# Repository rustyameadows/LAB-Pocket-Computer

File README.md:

# LAB Pocket Computer

[Rev 3A audio revision and volume build budget](hardware/rev-3a/LAB-Pocket-R3A-handoff-r1.md) includes the routed stereo audio update, factory exports and 500- and 1,000-device cost comparisons.

[Rev 3 manufacturing handoff and build costs](hardware/rev-3/LAB-Pocket-R3-manufacturing-handoff-r2.md) covers the corrected switch BOM, factory sourcing holds, prototype budget, KiCad project and upload files.

[Rev 2 bonded-core design](hardware/rev-2/README.md) includes the narrower PCB, matched top-entry card slots, centered camera, exposed Jauch pack and an actual-size review drawing.

A pocket-sized creative computer for making, playing and living with tiny programs.

LAB combines the tactile character of a Pocket Operator, the playful immediacy of a Game Boy, the programmability of a calculator and the openness of a microcontroller development board. It is a platform for small games, visual and musical instruments, personal utilities, experiments and ambient desk displays.

Make an app on your computer, with or without a coding agent. Preview it in a virtual LAB, install it on the physical device, then play with it or leave it on your desk doing something delightful.

## Bare-board Rev A

The [first hardware revision](hardware/rev-a/README.md) includes an editable KiCad project, a full-size fit drawing, a Blender assembly, three renders and the component datasheet archive. Its 82 × 146 mm PCB has fourteen exposed touch pads, sixteen switches and clear outside corners. [Front render](hardware/rev-a/renders/front.png) · [Schematic PDF](hardware/rev-a/review/LAB-Pocket-schematics.pdf)

## Initial hardware direction

- ESP32-S3 host as the original baseline; ESP32-P4 with a separate wireless processor (e.g. ESP32-C6) is the leading camera-capable host candidate.
- Independently programmable RP2350B user processor with its own memory and flash.
- Approximately 2.73-inch square 320 × 320 color IPS display.
- Sixteen tactile buttons with app-specific mappings.
- Proposed dual capacitive touch rails, seven segments on each side of the display (14 independent touch zones).
- Factory-installed, service-replaceable internal microSD (32 GB working target) plus a separate externally accessible microSD expansion/import slot; dedicated firmware flash remains separate.
- Rear-facing programmable color camera: Seeed IMX219 (8 MP MIPI CSI-2) is the lead candidate, with ST VD66GY global shutter (1.5 MP) as a specialized alternative.
- Twelve individually addressable rear-facing RGB LEDs and raised feet for an ambient pool of light.
- USB-C rechargeable power: a thin, service-replaceable ~5,000 mAh flat LiPo is the lead concept; two 21700 Li-ion cells are an alternative form factor with roughly twice the energy and a possible integrated desk stand.
- Four sensitive digital MEMS microphones with independent channels; two ultra-thin stereo speakers (four-speaker alternative) and a required 3.5 mm CTIA TRRS headset jack with stereo output and mono microphone input.
- Bosch BMI270 six-axis IMU and rear-facing Vishay VEML3328 colorscope with white illumination; optional separate ambient light sensor and expansion.
- Raw PCB and enclosed editions.

The host manages the device and its peripherals. The user processor is a playground that developers can program through an SDK, native code or replacement firmware. Independent recovery is a key design goal.

## Documentation

| Document | Purpose |
| --- | --- |
| [Product brief](docs/product-brief.md) | Vision, use cases, product principles and scope |
| [Hardware architecture](docs/hardware-architecture.md) | Dual processors, peripherals, communications, power and recovery |
| [Preliminary BOM](docs/bom.md) | Candidate components, rough unit costs and sourcing assumptions |
| [Developer ecosystem](docs/developer-ecosystem.md) | SDK, virtual device, native development and agent integrations |
| [Starter applications](docs/starter-apps.md) | Candidate built-in apps and what they teach |
| [Prototype roadmap](docs/prototype-roadmap.md) | Learning sequence, benchmarks and decision gates |
| [Industrial design references](docs/design-references.md) | Original notebook sketch and generated open-board concept |

## Project status

Concept and feasibility stage. The current hardware configuration is a working hypothesis, not a finalized design. The original preliminary cost model was $46.40 for a raw-board device at 1,000 units, including assembly, display and battery. The dual-card storage, touch rails, rear camera, revised battery/power system, revised audio and possible host/wireless changes are not yet fully priced; see the updated BOM. These are not supplier quotations.

First milestone: connect development boards, a representative display, buttons and RGB LEDs. Demonstrate a color instrument, responsive 2D graphics, interprocessor communication and recovery from crashed user firmware. Measure performance and power before committing to custom PCBA.

The Rev A schematics and layout are at design-review stage. Production firmware, full routing, supplier qualification and bench validation remain open. Licensing is undecided.

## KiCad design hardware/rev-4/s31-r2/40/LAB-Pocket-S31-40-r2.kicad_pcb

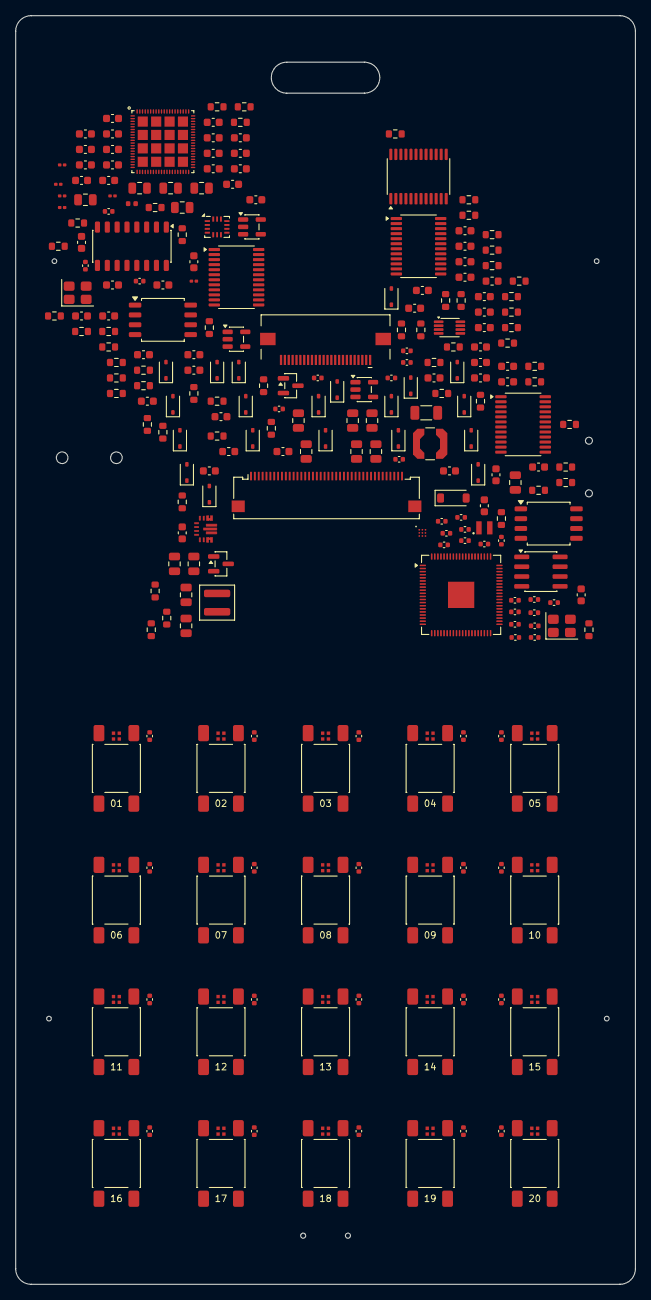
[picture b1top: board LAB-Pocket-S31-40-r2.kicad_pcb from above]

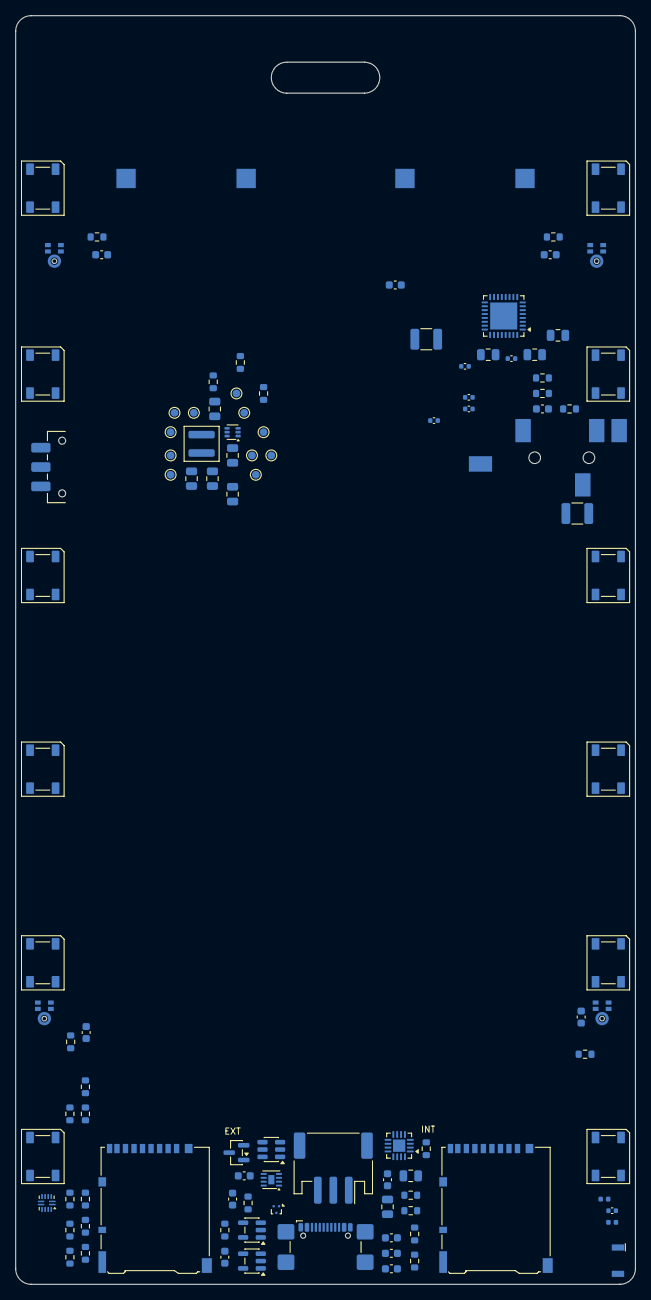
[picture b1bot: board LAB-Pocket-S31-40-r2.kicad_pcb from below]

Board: 8 copper layers, 80.0 x 163.8 mm, 372 parts (106 on the bottom side), 264 nets, no tracks yet.

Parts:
ANT401: 2450AT18A0100001E; Johanson-2450AT18A0100001E
C1, C5, C6, C7, C8, C9, C10, C11, C14, C17, C41, C42, C43, C46, C47, C401, C402, C403, C404, C410, C412, C413, C415, C417, C418, C421, C425, C502, C503, C505, C507, C508, C509, C510, C511, C516, C517: 100n; C_0603_1608Metric
C13: 470n; C_0603_1608Metric
C18, C44, C45, C145, C156, C157, C158, C406, C408, C411, C414, C416, C420, C424, C501, C504: 1u; C_0603_1608Metric
C19, C20, C146, C154, C155: 4.7u; C_0805_2012Metric
C21, C22, C23, C24, C25, C26, C27, C28, C29, C30, C31, C32, C33, C34, C35, C36, C37, C38, C39, C40, C111, C114, C115, C116, C117, C118, C119, C120, C121, C122, C123, C124, C125, C126, C127, C149, C150, C151, C152, C153, C159, C160, C161: 100n; C_0402_1005Metric
C48, C49, C50, C51, C52, C53, C54, C55, C56, C57, C58, C59, C60, C61, C62, C63, C162, C163, C164, C409, C419: 10u; C_0805_2012Metric
C108, C109, C110, C506, C512, C513, C514, C515: 4.7u; C_0402_1005Metric
C112, C113, C422, C423: 15p; C_0603_1608Metric
C147, C148: 100u; C_1210_3225Metric
C405, C407: 10n; C_0603_1608Metric
C426, C427: 1.5p; C_0201_0603Metric
C428: 1p; C_0402_1005Metric
C601, C602, C606: 1 uF / 25 V; C_0603_1608Metric
C603: 2.2 uF / 50 V; C_1206_3216Metric
C604: 330 nF / 16 V; C_0603_1608Metric
C605: 100 nF / 50 V; C_0603_1608Metric
D1, D2, D3, D4, D5, D6, D7, D8, D9, D10, D11, D12, D13, D14, D15, D16, D18, D19, D20, D21: BAS316; D_SOD-323
D22: TPD2EUSB30DRTR; Texas_DRT-3
D601: MBR0540 / Schottky; D_SOD-123
FB501, FB502: 120R at 100 MHz; L_0603_1608Metric
J1: USB4110-GF-A; USB4110-v5
J3: DM3AT • INT; microSD_HC_Hirose_DM3AT-SF-PEJM5
J4: DM3AT • EXT; microSD_HC_Hirose_DM3AT-SF-PEJM5
J5: SJ-43515TS-SMT; SJ-43515TS
J6: JST PH • keyed harness; JST_PH_S3B-PH-SM4-TB_1x03-1MP_P2.00mm_Horizontal
J501: Seeed 114993115 AF flex; JUSHUO_AFC01-S24FCC-00
J601: XF2M-4015-1A / RGB FPC; Omron_XF2M-4015-1A_1x40-1MP_P0.5mm_Horizontal
L1: 1.5uH; L_Coilcraft_XAL4020-XXX
L2: 1.0uH; L_Coilcraft_XAL4020-XXX
L4: 3.3uH; Abracon-AOTA-B201610-R3
L401: 2n / 35mOhm; L_0402_1005Metric
L402: 24n; L_0201_0603Metric
L403: 2.7n; L_0201_0603Metric
L404: 2.7n; L_0402_1005Metric
L405: 3.9n; L_0402_1005Metric
L406: DNP / RF tune; L_0201_0603Metric
L601: 4.7 uH; L_Coilcraft_LPS4018
LED1, LED2, LED3, LED4, LED5, LED6, LED7, LED8, LED9, LED10, LED11, LED12: WS2812B-V6
LED13, LED14, LED15, LED16, LED17, LED18, LED19, LED20, LED21, LED22, LED23, LED24, LED25, LED26, LED27, LED28, LED29, LED30, LED31, LED32: SK6805-EC10-000; SK6805-EC10-v5
LS1, LS2: PUI 8R / 1 W; PUI-AS01808AO-spring-v7
MK1, MK2, MK3, MK4: IM70D122V01; IM70D122
Q1: 2N7002-7-F; SOT-23
Q501: 2N7002; SOT-23
R1, R2, R3, R4, R22, R23, R24, R29, R35, R37, R38, R39, R62, R71, R401, R402, R403, R404, R406, R501, R502, R505, R507, R510, R603, R604: 10k; R_0603_1608Metric
R6, R7, R8, R9, R10, R11, R12, R13, R25, R34, R69: 47k; R_0603_1608Metric
R14, R15, R16, R17, R20: 100R; R_0603_1608Metric
R18, R19, R45, R503, R504, R506: 4.7k; R_0603_1608Metric
R26, R63: 1k; R_0603_1608Metric
R27: 1.5k; R_0603_1608Metric
R30, R33, R44, R47, R72, R73: 100k; R_0603_1608Metric
R31, R70: 1M; R_0603_1608Metric
R32: 169k; R_0603_1608Metric
R36: 68k; R_0603_1608Metric
R40, R41: 1.8M; R_0603_1608Metric
R42: 10.2k; R_0603_1608Metric
R43: 30.9k; R_0603_1608Metric
R46: 732k; R_0603_1608Metric
R61, R605: 33R; R_0603_1608Metric
R68, R74: 2.2k; R_0603_1608Metric
R405: 499; R_0603_1608Metric
R410, R411, R412, R413, R414, R415: 0; R_0603_1608Metric
R416: 0 / RF tune; R_0201_0603Metric
R508, R509: 22R; R_0603_1608Metric
R601: 63.4k; R_0603_1608Metric
R602: 10R; R_0603_1608Metric
SW1, SW2, SW3, SW4, SW5, SW6, SW7, SW8, SW9, SW10, SW11, SW12, SW13, SW14, SW15, SW16, SW17, SW18, SW19, SW20: TL3301; TL3301-key-v5
SW21: System power; SW_SPDT_CK_JS102011SAQN
TP1: RP_SWCLK; TestPoint_Pad_D1.0mm
TP2: RP_SWDIO; TestPoint_Pad_D1.0mm
TP3: RP_RUN_N; TestPoint_Pad_D1.0mm
TP4, TP405: GND; TestPoint_Pad_D1.0mm
TP5, TP406: 3V3; TestPoint_Pad_D1.0mm
TP401: HOST_BOOT_N; TestPoint_Pad_D1.0mm
TP402: HOST_EN; TestPoint_Pad_D1.0mm
TP403: HOST_TX; TestPoint_Pad_D1.0mm
TP404: HOST_RX; TestPoint_Pad_D1.0mm
U1: ESP32-S31NRV16; S31-QFN80
U2: RP2350B; QFN-80-1EP_10x10mm_P0.4mm_EP3.4x3.4mm
U4, U401: PCA9555PWR; TSSOP-24_4.4x7.8mm_P0.65mm
U6: BMI270; Bosch_LGA-14_3x2.5mm_P0.5mm
U8: SN74AHCT1G125DBVR; SOT-23-5
U9, U10: W25Q128JVSIQ; SOIC-8_5.3x5.3mm_P1.27mm
U11: BQ24074RGTR; VQFN-16-1EP_3x3mm_P0.5mm_EP1.6x1.6mm
U12: TPS3700DDCR; TSOT-23-6
U13: MAX17048G+T10; TDFN-8-1EP_2x2mm_P0.5mm_EP0.8x1.2mm
U14: TUSB320LAIRWBR; Texas_X2QFN-12_1.6x1.6mm_P0.4mm
U15: SN74LVC1G04DBVR; SOT-23-5
U16: TLV75533PDBVR; SOT-23-5
U17: TPS3839G33DBZR; SOT-23
U18: TPS63070RNMR; TPS63070-RNM-R3
U19: TPS61023DRLR; SOT-563
U22: APS6404L-3SQR-SN; SOIC-8_3.9x4.9mm_P1.27mm
U31: NAU88C22YG; VQFN-32-1EP_5x5mm_P0.5mm_EP3.5x3.5mm
U32: PAM8406DR; PAM8406-SO16-DS43342
U501: TLV75518PDBVR; SOT-23-5
U502: TLV75728PDBVR; SOT-23-5
U503, U504: SN74AXC8T245PWR; TSSOP-24_4.4x7.8mm_P0.65mm
U505: TCA9406DCUR; VSSOP-8_2.3x2mm_P0.5mm
U601: TPS61163A / dual WLED; TI_YFF0009_TPS61163A
Y1: 40MHz, CL 10pF; Crystal_SMD_3225-4Pin_3.2x2.5mm
Y2: ABM8-272-T3; Crystal_SMD_3225-4Pin_3.2x2.5mm

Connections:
3V3: C1.1, C5.1, C6.1, C7.1, C8.1, C9.1, C10.1, C11.1, C13.1, C17.1, C51.1, C52.1, C53.1, C54.1, C55.1, C56.1, C57.1, C58.1, C108.1, C111.1, C114.1, C115.1, C116.1, C117.1, C118.1, C119.1, C120.1, C121.1, C122.1, C123.1, C124.1, C149.1, C150.1, C151.1, C152.1, C153.1, C154.1, C155.1, C159.1, C160.1, C161.1, C162.1, C163.1, C164.1, C401.1, C402.1, C403.1, C404.1, C405.1, C406.1, C407.1, C408.1, C409.1, C411.1, C412.1, C419.1, C425.1, C508.1, C510.1, C512.1, C514.1, C517.1, C605.1, C606.1, J3.4 (VDD), J4.4 (VDD), J601.5 (VCI), L401.1, MK1.1 (VDD), MK2.1 (VDD), MK2.4 (LR), MK3.1 (VDD), MK4.1 (VDD), MK4.4 (LR), R1.1, R2.1, R3.1, R4.1, R6.1, R7.1, R8.1, R9.1, R10.1, R11.1, R12.1, R13.1, R18.1, R19.1, R22.1, R23.1, R29.1, R37.1, R38.1, R39.1, R43.1, R61.1, R62.1, R70.1, R401.1, R402.1, R403.1, R406.1, R505.2, R507.2, R604.1, TP5.1 (1_1), TP406.1 (PAD_1), U1.11 (VDDPST_1), U1.43 (VCCA/VDDPST_2), U1.54 (VDDPST_3), U1.64 (VDDPST_4), U1.77 (VDDA1), U1.80 (VDDA2), U2.5 (IOVDD), U2.15 (IOVDD), U2.24 (IOVDD), U2.29 (IOVDD), U2.41 (IOVDD), U2.50 (IOVDD), U2.59 (ADC_AVDD), U2.60 (IOVDD), U2.64 (VREG_VIN), U2.68 (USB_OTP_VDD), U2.69 (QSPI_IOVDD), U2.76 (IOVDD), U4.24 (VDD), U6.5 (VDDIO), U6.8 (VDD), U6.12 (CSB), U10.8 (VCC), U18.7 (VOUT), U18.8 (VOUT), U22.8 (VCC), U31.13 (VDDC), U31.14 (VDDB), U31.26 (VDDSPK), U31.31 (VDDA), U32.4 (PVDDL), U32.5 (MUTE_N), U32.6 (VDD), U32.9 (MODE), U32.13 (PVDDR), U401.21 (A0), U401.24 (VCC), U501.1 (IN), U502.1 (IN), U503.1 (VCCA), U504.1 (VCCA), U504.2 (DIR1), U504.11 (DIR2), U505.7 (VCCB)
AMP_AC_L: C156.2, R72.1
AMP_AC_R: C157.2, R73.1
AMP_ENABLE: R74.1, U31.15 (CSB_GPIO1), U32.12 (SHDN_N)
AMP_IN_L: R72.2, U32.7 (INL)
AMP_IN_R: R73.2, U32.10 (INR)
AMP_VREF: C158.1, U32.8 (VREF)
BL_PWM: U1.55 (GPIO42), U601.B1 (PWM)
BMI_ADDR: R71.1, U6.1 (SDO)
BUS_CLK: J3.5 (CLK), J4.5 (CLK), U1.32 (GPIO24/SDIO_CLK), U2.18 (GPIO18)
BUS_MISO: J3.7 (DAT0), J4.7 (DAT0), U1.29 (GPIO22/SDIO_D2), U2.19 (GPIO19)
BUS_MOSI: J3.3 (CMD), J4.3 (CMD), U1.31 (GPIO23/SDIO_D3), U2.16 (GPIO16)
CAM_1V8: C503.1, C509.1, C511.1, C513.1, C516.1, J501.14 (F11_DOVDD), R502.2, U501.5 (OUT), U503.23 (VCCB_1), U503.24 (VCCB_2), U504.23 (VCCB_1), U504.24 (VCCB_2), U505.3 (VCCA), U505.6 (OE)
CAM_2V8: C515.1, FB501.1, FB502.1, U502.5 (OUT)
CAM_AF_2V8: C506.1, C507.1, FB502.2, J501.1 (F24_AFVDD)
CAM_ANALOG_ENABLE: Q501.1 (G), R504.1, U401.10 (P06), U502.3 (EN)
CAM_AVDD_2V8: C504.1, C505.1, FB501.2, J501.21 (F04_AVDD)
CAM_BUS_OE_N: Q501.3 (D), R507.1, U503.22 (OE_N), U504.22 (OE_N)
CAM_D0: U1.59 (GPIO46), U503.3 (A1)
CAM_D0_1V8: J501.6 (F19_Y2), U503.21 (B1)
CAM_D1: U1.60 (GPIO47), U503.4 (A2)
CAM_D1_1V8: J501.4 (F21_Y3), U503.20 (B2)
CAM_D2: U1.61 (GPIO48), U503.5 (A3)
CAM_D2_1V8: J501.3 (F22_Y4), U503.19 (B3)
CAM_D3: U1.62 (GPIO49), U503.6 (A4)
CAM_D3_1V8: J501.5 (F20_Y5), U503.18 (B4)
CAM_D4: U1.65 (GPIO50), U503.7 (A5)
CAM_D4_1V8: J501.7 (F18_Y6), U503.17 (B5)
CAM_D5: U1.66 (GPIO51), U503.8 (A6)
CAM_D5_1V8: J501.9 (F16_Y7), U503.16 (B6)
CAM_D6: U1.67 (GPIO52), U503.9 (A7)
CAM_D6_1V8: J501.11 (F14_Y8), U503.15 (B7)
CAM_D7: U1.68 (GPIO53), U503.10 (A8)
CAM_D7_1V8: J501.13 (F12_Y9), U503.14 (B8)
CAM_DVDD_INT: C501.1, C502.1, J501.15 (F10_DVDD_INT)
CAM_ENABLE: R503.1, U4.18 (IO1_5), U501.3 (EN)
CAM_HREF: U1.72 (GPIO57/MTMS), U504.8 (A6)
CAM_HREF_1V8: J501.16 (F09_HREF), U504.16 (B6)
CAM_PCLK: R509.2, U1.69 (GPIO54/MTDO)
CAM_PCLK_1V8: J501.8 (F17_PCLK), U504.17 (B5)
CAM_PCLK_DRV: R509.1, U504.7 (A5)
CAM_PWDN: R505.1, U401.9 (P05), U504.4 (A2)
CAM_PWDN_1V8: J501.17 (F08_PWDN), R502.1, U504.20 (B2)
CAM_RESET_N: R506.1, U401.8 (P04), U504.5 (A3)
CAM_RESET_N_1V8: J501.19 (F06_RESETB), R501.1, U504.19 (B3)
CAM_SCL_1V8: J501.20 (F05_SCL), U505.5 (SCL_A)
CAM_SDA_1V8: J501.22 (F03_SDA), U505.4 (SDA_A)
CAM_VSYNC: U1.71 (GPIO56/MTDI), U504.9 (A7)
CAM_VSYNC_1V8: J501.18 (F07_VSYNC), U504.15 (B7)
CAM_XCLK: R510.1, U1.70 (GPIO55/MTCK), U504.3 (A1)
CAM_XCLK_1V8: J501.12 (F13_MCLK), R508.2
CAM_XCLK_DRV_1V8: R508.1, U504.21 (B1)
CC1: J1.A5 (CC1), U14.1 (CC1)
CC2: J1.B5 (CC2), U14.2 (CC2)
CC_3V3: C43.1, C44.1, C46.1, R24.1, U14.12 (VDD), U15.5 (VCC), U16.5 (OUT)
CC_HIGH_N: R24.2, U14.7 (OUT1), U15.2 (A)
CC_VBUS_DET: R40.2, R41.2, U14.4 (VBUS_DET)
CHARGE_TIMER: R36.1, U11.14 (TMR)
CHARGING_N: R39.2, U4.9 (IO0_5), U11.9 (~CHG)
CHG_CE_N: Q1.3 (D), R35.2, U11.4 (~CE)
CHG_ISET: R26.1, U11.16 (ISET)
CODEC_VMID: C146.1, U31.27 (VREF)
COLD_SENSE: R32.2, R33.1, U12.4 (INB-)
FUEL_ALERT_N: R37.2, U4.11 (IO0_7), U13.5 (ALRT)
GND: C1.2, C5.2, C6.2, C7.2, C8.2, C9.2, C10.2, C11.2, C13.2, C14.2, C17.2, C18.2, C19.2, C20.2, C21.2, C22.2, C23.2, C24.2, C25.2, C26.2, C27.2, C28.2, C29.2, C30.2, C31.2, C32.2, C33.2, C34.2, C35.2, C36.2, C37.2, C38.2, C39.2, C40.2, C41.2, C42.2, C43.2, C44.2, C45.2, C46.2, C47.2, C48.2, C49.2, C50.2, C51.2, C52.2, C53.2, C54.2, C55.2, C56.2, C57.2, C58.2, C59.2, C60.2, C61.2, C62.2, C63.2, C108.2, C109.2, C110.2, C111.2, C112.2, C113.2, C114.2, C115.2, C116.2, C117.2, C118.2, C119.2, C120.2, C121.2, C122.2, C123.2, C124.2, C125.2, C126.2, C127.2, C146.2, C149.2, C150.2, C151.2, C152.2, C153.2, C154.2, C155.2, C158.2, C159.2, C160.2, C161.2, C162.2, C163.2, C164.2, C401.2, C402.2, C403.2, C404.2, C405.2, C406.2, C407.2, C408.2, C409.2, C410.2, C411.2, C412.2, C413.2, C414.2, C415.2, C416.2, C417.2, C418.2, C419.2, C420.2, C421.2, C422.2, C423.2, C424.2, C425.2, C426.2, C427.2, C501.2, C502.2, C503.2, C504.2, C505.2, C506.2, C507.2, C508.2, C509.2, C510.2, C511.2, C512.2, C513.2, C514.2, C515.2, C516.2, C517.2, C601.2, C602.2, C603.2, C604.2, C605.2, C606.2, D22.3 (GND), J1.A1 (GND), J1.A12 (GND), J1.B1 (GND), J1.B12 (GND), J1.SH (SHIELD), J3.6 (VSS), J3.10 (DET_A), J3.SH (SHIELD), J4.6 (VSS), J4.10 (DET_A), J4.SH (SHIELD), J5.4 (Ring2), J6.1, J501.2 (F23_AF_GND), J501.10 (F15_DGND), J501.23 (F02_AGND), J501.25 (HOLD_L), J501.26 (HOLD_R), J601.4 (GND), J601.16 (B0), J601.28 (R0), J601.34 (GND), J601.40 (GND), L404.2, L406.2, LED1.3 (VSS), LED2.3 (VSS), LED3.3 (VSS), LED4.3 (VSS), LED5.3 (VSS), LED6.3 (VSS), LED7.3 (VSS), LED8.3 (VSS), LED9.3 (VSS), LED10.3 (VSS), LED11.3 (VSS), LED12.3 (VSS), LED13.1 (VSS), LED14.1 (VSS), LED15.1 (VSS), LED16.1 (VSS), LED17.1 (VSS), LED18.1 (VSS), LED19.1 (VSS), LED20.1 (VSS), LED21.1 (VSS), LED22.1 (VSS), LED23.1 (VSS), LED24.1 (VSS), LED25.1 (VSS), LED26.1 (VSS), LED27.1 (VSS), LED28.1 (VSS), LED29.1 (VSS), LED30.1 (VSS), LED31.1 (VSS), LED32.1 (VSS), MK1.4 (LR), MK1.5 (GND), MK2.5 (GND), MK3.4 (LR), MK3.5 (GND), MK4.5 (GND), Q1.2 (S), Q501.2 (S), R25.2, R26.2, R27.2, R31.2, R33.2, R36.2, R42.2, R44.2, R45.2, R47.2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
HEADSET_MIC: C145.1, J5.1 (Sleeve), R68.2
HOST_BOOT_N: R402.2, TP401.1 (PAD_1), U1.76 (GPIO61)
HOST_EN: C424.1, R401.2, TP402.1 (PAD_1), U1.4 (CHIP_PU)
HOST_FLASH_VDD: C420.1, C421.1, R404.1, U1.39 (VDD_SPI), U9.8 (VCC)
HOST_NOR_CLK: R414.2, U9.6 (CLK)
HOST_NOR_CS_N: R404.2, R410.2, U9.1 (CS#)
HOST_NOR_D0: R415.2, U9.5 (DI/IO0)
HOST_NOR_D1: R411.2, U9.2 (DO/IO1)
HOST_NOR_D2: R412.2, U9.3 (WP#/IO2)
HOST_NOR_D3: R413.2, U9.7 (HOLD#/IO3)
HOST_RX: TP404.1 (PAD_1), U1.74 (GPIO59/U0RXD)
HOST_TX: R405.2, TP403.1 (PAD_1)
HOST_XTAL_N: C423.1, U1.78 (XTAL_N), Y1.3 (XTAL)
HOST_XTAL_P: C422.1, L402.2, Y1.1 (XTAL)
HOT_SENSE: R30.2, R31.1, U12.3 (INA+)
HP_L: C147.2, J5.2 (Tip), R69.1
HP_R: C148.2, J5.3 (Ring1)
HP_RAW_L: C147.1, U31.30 (LHP)
HP_RAW_R: C148.1, U31.29 (RHP)
HP_TIP_SWITCH: J5.5 (TipSwitch), R70.2, U31.3 (LLIN_GPIO2)
I2S_ADC: U1.27 (GPIO20/SDIO_D0), U31.9 (ADCOUT)
I2S_BCLK: U1.12 (GPIO6), U31.8 (BCLK)
I2S_DAC: U1.28 (GPIO21/SDIO_D1), U31.10 (DACIN)
I2S_LRCLK: U1.13 (GPIO7), U31.7 (FS)
I2S_MCLK: U1.10 (GPIO5), U31.11 (MCLK)
ILIM_SET: R27.1, U11.12 (ILIM)
IMU_INT: U1.51 (GPIO38), U6.4 (INT1)
KEY_C0: R1.2, SW1.2, SW6.2, SW11.2, SW16.2, U4.13 (IO1_0)
KEY_C1: R2.2, SW2.2, SW7.2, SW12.2, SW17.2, U4.14 (IO1_1)
KEY_C2: R3.2, SW3.2, SW8.2, SW13.2, SW18.2, U4.15 (IO1_2)
KEY_C3: R4.2, SW4.2, SW9.2, SW14.2, SW19.2, U4.16 (IO1_3)
KEY_C4: R29.2, SW5.2, SW10.2, SW15.2, SW20.2, U4.17 (IO1_4)
KEY_R0: D1.1 (K), D2.1 (K), D3.1 (K), D4.1 (K), D5.1 (K), U4.4 (IO0_0)
KEY_R1: D6.1 (K), D7.1 (K), D8.1 (K), D9.1 (K), D10.1 (K), U4.5 (IO0_1)
KEY_R2: D11.1 (K), D12.1 (K), D13.1 (K), D14.1 (K), D15.1 (K), U4.6 (IO0_2)
KEY_R3: D16.1 (K), D18.1 (K), D19.1 (K), D20.1 (K), D21.1 (K), U4.7 (IO0_3)
KEY_RGB_01: LED13.4 (DOUT), LED14.2 (DIN)
KEY_RGB_02: LED14.4 (DOUT), LED15.2 (DIN)
KEY_RGB_03: LED15.4 (DOUT), LED16.2 (DIN)
KEY_RGB_04: LED16.4 (DOUT), LED17.2 (DIN)
KEY_RGB_05: LED17.4 (DOUT), LED18.2 (DIN)
KEY_RGB_06: LED18.4 (DOUT), LED19.2 (DIN)
KEY_RGB_07: LED19.4 (DOUT), LED20.2 (DIN)
KEY_RGB_08: LED20.4 (DOUT), LED21.2 (DIN)
KEY_RGB_09: LED21.4 (DOUT), LED22.2 (DIN)
KEY_RGB_10: LED22.4 (DOUT), LED23.2 (DIN)
KEY_RGB_11: LED23.4 (DOUT), LED24.2 (DIN)
KEY_RGB_12: LED24.4 (DOUT), LED25.2 (DIN)
KEY_RGB_13: LED25.4 (DOUT), LED26.2 (DIN)
KEY_RGB_14: LED26.4 (DOUT), LED27.2 (DIN)
KEY_RGB_15: LED27.4 (DOUT), LED28.2 (DIN)
KEY_RGB_16: LED28.4 (DOUT), LED29.2 (DIN)
KEY_RGB_17: LED29.4 (DOUT), LED30.2 (DIN)
KEY_RGB_18: LED30.4 (DOUT), LED31.2 (DIN)
KEY_RGB_19: LED31.4 (DOUT), LED32.2 (DIN)
KEY_RGB_IN: LED12.2 (DOUT), LED13.2 (DIN)
LCD_B0: J601.17 (B1), U1.14 (GPIO8)
LCD_B1: J601.18 (B2), U1.15 (GPIO9)
LCD_B2: J601.19 (B3), U1.16 (GPIO10)
LCD_B3: J601.20 (B4), U1.17 (GPIO11)
LCD_B4: J601.21 (B5), U1.19 (GPIO12)
LCD_BL_COMP: C604.1, U601.B2 (COMP)
LCD_BL_ISET: R601.1, U601.A1 (ISET)
LCD_BL_SW: D601.2 (A), L601.2, U601.C3 (SW)
LCD_BL_VIN: C602.1, R602.2, U601.C1 (EN), U601.C2 (VIN)
LCD_CS: J601.11 (CS), R604.2, U401.4 (P00)
LCD_DE: J601.13 (DE), U1.56 (GPIO43)
LCD_G0: J601.22 (G0), U1.20 (GPIO13)
LCD_G1: J601.23 (G1), U1.21 (GPIO14)
LCD_G2: J601.24 (G2), U1.22 (GPIO15)
LCD_G3: J601.25 (G3), U1.23 (GPIO16)
LCD_G4: J601.26 (G4), U1.24 (GPIO17)
LCD_G5: J601.27 (G5), U1.25 (GPIO18)
LCD_HSYNC: J601.15 (HSYNC), U1.57 (GPIO44)
LCD_LED_A: C603.1, D601.1 (K), J601.1 (LEDA)
LCD_LED_K1: J601.2 (LEDK1), U601.A3 (IFB1)
LCD_LED_K2: J601.3 (LEDK2), U601.A2 (IFB2)
LCD_PCLK: R605.1, U1.53 (GPIO40)
LCD_PCLK_FPC: J601.12 (PCLK), R605.2
LCD_R0: J601.29 (R1), U1.26 (GPIO19)
LCD_R1: J601.30 (R2), U1.46 (GPIO33)
LCD_R2: J601.31 (R3), U1.47 (GPIO34)
LCD_R3: J601.32 (R4), U1.48 (GPIO35)
LCD_R4: J601.33 (R5), R403.2, U1.49 (GPIO36)
LCD_RESET_N: J601.6 (RESET), R603.1, U401.7 (P03)
LCD_SCK: J601.10 (SCK), U401.5 (P01)
LCD_SDI: J601.9 (SDA), U401.6 (P02)
LCD_VSYNC: J601.14 (VSYNC), U1.58 (GPIO45)
LED_5V_SW: C14.1, C21.1, C22.1, C23.1, C24.1, C25.1, C26.1, C27.1, C28.1, C29.1, C30.1, C31.1, C32.1, C33.1, C34.1, C35.1, C36.1, C37.1, C38.1, C39.1, C40.1, C61.1, C62.1, C63.1, LED1.1 (VDD), LED2.1 (VDD), LED3.1 (VDD), LED4.1 (VDD), LED5.1 (VDD), LED6.1 (VDD), LED7.1 (VDD), LED8.1 (VDD), LED9.1 (VDD), LED10.1 (VDD), LED11.1 (VDD), LED12.1 (VDD), LED13.3 (VDD), LED14.3 (VDD), LED15.3 (VDD), LED16.3 (VDD), LED17.3 (VDD), LED18.3 (VDD), LED19.3 (VDD), LED20.3 (VDD), LED21.3 (VDD), LED22.3 (VDD), LED23.3 (VDD), LED24.3 (VDD), LED25.3 (VDD), LED26.3 (VDD), LED27.3 (VDD), LED28.3 (VDD), LED29.3 (VDD), LED30.3 (VDD), LED31.3 (VDD), LED32.3 (VDD), R46.1, U8.5 (VCC), U19.6 (VOUT)
LED_ENABLE: R45.1, U4.8 (IO0_4), U19.2 (EN)
LINE_L: C156.1, U31.22 (AUXOUT2)
LINE_R: C157.1, U31.21 (AUXOUT1)
MIC_AC: C145.2, U31.1 (LMICP)
MIC_BIAS: R68.1, U31.32 (MICBIAS)
MIC_RAW_1: MK1.3 (DATA), R14.1
MIC_RAW_2: MK2.3 (DATA), R15.1
MIC_RAW_3: MK3.3 (DATA), R16.1
MIC_RAW_4: MK4.3 (DATA), R17.1
unnamed: D1.2 (A), SW1.1
unnamed: D2.2 (A), SW2.1
unnamed: D3.2 (A), SW3.1
unnamed: D4.2 (A), SW4.1
unnamed: D5.2 (A), SW5.1
unnamed: D6.2 (A), SW6.1
unnamed: D7.2 (A), SW7.1
unnamed: D8.2 (A), SW8.1
unnamed: D9.2 (A), SW9.1
unnamed: D10.2 (A), SW10.1
unnamed: D11.2 (A), SW11.1
unnamed: D12.2 (A), SW12.1
unnamed: D13.2 (A), SW13.1
unnamed: D14.2 (A), SW14.1
unnamed: D15.2 (A), SW15.1
unnamed: D16.2 (A), SW16.1
unnamed: D18.2 (A), SW17.1
unnamed: D19.2 (A), SW18.1
unnamed: D20.2 (A), SW19.1
unnamed: D21.2 (A), SW20.1
unnamed: LED1.2 (DOUT), LED2.4 (DIN)
unnamed: LED2.2 (DOUT), LED3.4 (DIN)
unnamed: LED3.2 (DOUT), LED4.4 (DIN)
unnamed: LED5.2 (DOUT), LED6.4 (DIN)
unnamed: LED6.2 (DOUT), LED7.4 (DIN)
unnamed: LED7.2 (DOUT), LED8.4 (DIN)
unnamed: LED9.2 (DOUT), LED10.4 (DIN)
unnamed: LED10.2 (DOUT), LED11.4 (DIN)
unnamed: LED11.2 (DOUT), LED12.4 (DIN)
PACK_POS: C20.1, C42.1, J6.3, U11.2 (BAT), U11.3 (BAT), U13.2 (CELL), U13.3 (VDD)
PACK_TS: J6.2, R30.1, R32.1, U11.1 (TS)
PDM_A: R14.2, R15.2, U1.5 (GPIO0/XTAL32_N)
PDM_B: R16.2, R17.2, U1.6 (GPIO1/XTAL32_P)
PDM_CLK: MK1.2 (CLK), MK2.2 (CLK), MK3.2 (CLK), MK4.2 (CLK), U1.9 (GPIO4)
PIXEL_FB: R46.2, R47.1, U19.1 (FB)
PIXEL_SW: L2.2, U19.5 (SW)
REG_AUX: C47.1, U18.3 (VAUX)
REG_FB: R42.1, R43.2, U18.5 (FB)
REG_L1: L1.1, U18.11 (L1)
REG_L2: L1.2, U18.9 (L2)
RF_ANT_FEED: ANT401.1 (FEED_1), L405.2
RF_FEED_50R: C428.1, L406.1, R416.2
RF_TEE: C428.2, L404.1, L405.1
RGB_DATA_3V3: U1.52 (GPIO39), U8.2 (A)
RGB_DRIVE_5V: R20.1, U8.4 (Y)
RGB_IN: LED1.4 (DIN), R20.2
RGB_LINK_4: LED4.2 (DOUT), LED5.4 (DIN)
RGB_LINK_8: LED8.2 (DOUT), LED9.4 (DIN)
RP_CORE: C109.1, C125.1, C126.1, C127.1, L4.1, U2.10 (DVDD), U2.32 (DVDD), U2.51 (DVDD), U2.65 (VREG_FB)
RP_CS_N: R406.2, U1.33 (GPIO25/SDIO_CMD), U2.17 (GPIO17)
RP_RAM_CS_N: R62.2, U2.77 (GPIO0), U22.1 (CE_N)
RP_REG_AVDD: C110.1, R61.2, U2.61 (VREG_AVDD)
RP_REG_LX: L4.2, U2.63 (VREG_LX)
RP_RUN_N: R22.2, TP3.1 (1_1), U2.35 (RUN), U401.11 (P07)
RP_SWCLK: TP1.1 (1_1), U2.33 (SWCLK)
RP_SWDIO: TP2.1 (1_1), U2.34 (SWDIO)
RP_XIN: C112.1, U2.30 (XIN), Y2.1 (X1)
RP_XOUT: R63.1, U2.31 (XOUT)
RP_XTAL_2: C113.1, R63.2, Y2.3 (X2)
S31_ADC_REF: C418.1, U1.63 (VREF_ADC)
S31_ANT: C426.1, L403.1, U1.1 (ANT)
S31_NOR_CLK: R414.1, U1.41 (SPICLK)
S31_NOR_CS_N: R410.1, U1.36 (SPICS)
S31_NOR_D0: R415.1, U1.42 (SPID)
S31_NOR_D1: R411.1, U1.37 (SPIQ)
S31_NOR_D2: R412.1, U1.38 (SPIWP)
S31_NOR_D3: R413.1, U1.40 (SPIHD)
S31_PSRAM_1V8: C413.1, C414.1, C415.1, C416.1, C417.1, U1.30 (VDD_PSRAM_1P8_1), U1.34 (VDD_PSRAM_1P8_2), U1.35 (VDD_LDO_1P8)
S31_RF_MATCH: C427.1, L403.2, R416.1
S31_RF_VDD: C410.1, L401.2, U1.2 (VDDA3), U1.3 (VDDA4)
S31_UART0_TX: R405.1, U1.73 (GPIO58/U0TXD)
S31_XTAL_P: L402.1, U1.79 (XTAL_P)
SD_EXT_CS_N: J4.2 (DAT3/CD), R11.2, U1.75 (GPIO60)
SD_EXT_DAT1: J4.8 (DAT1), R12.2
SD_EXT_DAT2: J4.1 (DAT2), R10.2
SD_EXT_DET_N: J4.9 (DET_B), R13.2, U401.13 (P10)
SD_INT_CS_N: J3.2 (DAT3/CD), R7.2, U1.50 (GPIO37)
SD_INT_DAT1: J3.8 (DAT1), R8.2
SD_INT_DAT2: J3.1 (DAT2), R6.2
SD_INT_DET_N: J3.9 (DET_B), R9.2, U401.14 (P11)
SPK_L_N: LS1.2 (Minus), U32.3 (OUT_L_N)
SPK_L_P: LS1.1 (Plus), U32.1 (OUT_L_P)
SPK_R_N: LS2.2 (Minus), U32.14 (OUT_R_N)
SPK_R_P: LS2.1 (Plus), U32.16 (OUT_R_P)
SYSTEM_ENABLE: R44.1, SW21.2 (B), U18.14 (EN)
SYS_ABOVE_UVLO: SW21.3 (C), U17.2 (RESET_N)
SYS_SCL: R19.2, U1.8 (GPIO3), U4.22 (SCL), U6.13 (SCx), U13.7 (SCL), U31.16 (SCLK), U401.22 (SCL), U505.8 (SCL_B)
SYS_SDA: R18.2, U1.7 (GPIO2), U4.23 (SDA), U6.14 (SDx), U13.8 (SDA), U31.17 (SDIO), U401.23 (SDA), U505.1 (SDA_B)
TEMP_OK: Q1.1 (G), R34.2, U12.1 (OUTA), U12.6 (OUTB)
USB_D_N: D22.2 (D_N), J1.A7 (D-), J1.B7 (D-), U1.45 (USB_DM)
USB_D_P: D22.1 (D_P), J1.A6 (D+), J1.B6 (D+), U1.44 (USB_DP)
USB_HIGH_CURRENT: R25.1, U11.5 (EN2), U15.4 (Y)
USER_NOR_CLK: U2.71 (QSPI_SCLK), U10.6 (CLK), U22.6 (SCLK)
USER_NOR_CS_N: R23.2, U2.75 (~QSPI_SS), U10.1 (CS_N)
USER_NOR_D0: U2.72 (QSPI_SD0), U10.5 (IO0), U22.5 (SIO0)
USER_NOR_D1: U2.74 (QSPI_SD1), U10.2 (IO1), U22.2 (SIO1)
USER_NOR_D2: U2.73 (QSPI_SD2), U10.3 (IO2), U22.3 (SIO2)
USER_NOR_D3: U2.70 (QSPI_SD3), U10.7 (IO3), U22.7 (SIO3)
VBUS: C18.1, C41.1, C45.1, J1.A4 (VBUS), J1.A9 (VBUS), J1.B4 (VBUS), J1.B9 (VBUS), R34.1, R40.1, R41.1, U11.13 (IN), U12.5 (VDD), U16.1 (IN), U16.3 (EN)
VBUS_OK_N: R38.2, U4.10 (IO0_6), U11.7 (~PGOOD)
VSYS: C19.1, C48.1, C49.1, C50.1, C59.1, C60.1, C601.1, L2.1, L601.1, R35.1, R602.1, U11.10 (OUT), U11.11 (OUT), U17.3 (VDD), U18.12 (VIN), U18.13 (VIN), U19.3 (VIN)

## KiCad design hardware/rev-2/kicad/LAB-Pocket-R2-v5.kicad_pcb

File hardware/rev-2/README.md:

# LAB Pocket Computer · Rev 2

The Rev 2 bare board measures **74 × 146 mm**. The exposed Jauch pack bonds to the rear PCB. The nominal maximum-cycled stack is **14.97 mm** from the front display surface to the back of the pouch. Rev A measured 82 × 146 × 20.55 mm.

[Actual-size US Letter drawing](review/LAB-Pocket-R2-letter-v1-core.pdf) · [Rear render](renders/LAB-Pocket-R2-rear.png) · [Front render](renders/LAB-Pocket-R2-front.png) · [Full Blender assembly](blender/LAB-Pocket-R2.blend) · [Assembled GLB](blender/LAB-Pocket-R2-assembled.glb) · [KiCad project](kicad/LAB-Pocket-R2.kicad_pro) · [Nine schematic sheets](review/LAB-Pocket-R2-schematics.pdf)

## Mechanical layout

- The 59.5 mm pouch width sets the board width. Each side adds a 1.25 mm pouch-to-LED gap, a 5 mm LED body and 1 mm from that body to the PCB edge. The 53.54 mm LCD leaves 1.43 mm between its body and each 7.6 mm touch electrode. Switches retain their 17 × 16 mm pitch. All sixteen have individual references on the drawing.
- Both rear Hirose slots open toward the short top edge. From the rear, external J4 is on the left and internal J3 is on the right. Their origin points are 22 mm to either side of the centerline and 20.2 mm down from the top. Each slot has a clear card approach. J3 includes the seated card.
- The twelve LEDs form two six-pixel columns. LED12 starts at the upper left in rear view. Centers are 3.5 mm from the side edges, at 10.5, 35.5, 60.5, 85.5, 110.5 and 135.5 mm down the board. The top microphones moved below the top LEDs to keep the card approaches clear.
- The rear lens is directly behind the center of the active display at **37.00 mm from either side and 37.06 mm from the top**. This leaves 1.69 mm from the nominal camera carrier to the pouch. The headset jack moved to the lower side and the speakers moved down 3 mm for clearance.
- The guard, four feet, tabs, studs and guard mounting holes have been removed. The pouch is the outermost surface on the back.

## Pack and bond

The 4,800 mAh LP735977JH has a 59.5 × 78.5 mm maximum footprint. Jauch specifies 7.3 mm at delivery and 7.9 mm after cycling. The model uses the cycled envelope and includes a folded laminate rim, a shallow protection-board end, two separate wire exits, and label artwork taken from the manufacturer's drawing. The short-end details are visual approximations. Each modeled lead is 70 mm from its pad to its J6 terminal. The service loops and termination are proposed integration geometry. The supplier part comes with wire leads. [Jauch source drawing, p. 1](datasheets/LP735977JH.pdf)

Two candidate 20 × 55 mm strips of 3M 9495LE bond the pack to the rear solder mask. The installed tape thickness is 0.17 mm. The dimensional stack is 6.90 mm from the back of the PCB to the front display, plus 0.17 mm of bondline and 7.90 mm of pouch. The pack area excludes rear components and the matrix vias are tented on the pack side. [3M technical data](datasheets/3M-9495LE.pdf)

Confirm wrapper-to-adhesive compatibility with the pack supplier and validate retention, swelling clearance, insulation and wire dressing on a physical sample. The exposed pouch and its protection circuitry remain accessible to contact. Pocket carry, drops and abrasion require mechanical validation.

## Review status

KiCad and Blender checks confirm the dimensions above. PCB DRC reports **zero courtyard overlaps, keepout violations, shorts or schematic-parity mismatches**. Electrical completion is open. There are 388 unrouted connections and 108 inherited DRC violations, comprising 104 ESP32-P4 pad-clearance violations and four USB-C pad-to-hole clearance violations. ERC reports 143 errors and 18 warnings. Camera electrical integration, power, clocking, radio and high-speed routing require further work. Charging remains inhibited in the study schematic.

Run the board checker with the system Python containing KiCad 10's pcbnew module. The Blender checker reads the evaluated assembly at frame 1. The assembled GLB uses metres, while the Blender scene and drawing use millimetres. The second GLB contains the KiCad board export alone.

```sh
/usr/bin/python3 check-fit-R2.py
blender -b blender/LAB-Pocket-R2.blend --python-exit-code 1 -P check-scene-R2.py
```

[Rev 2 BOM](parts.csv) · [Index and SHA-256 digests for all 32 supplier documents](datasheets/index.csv)

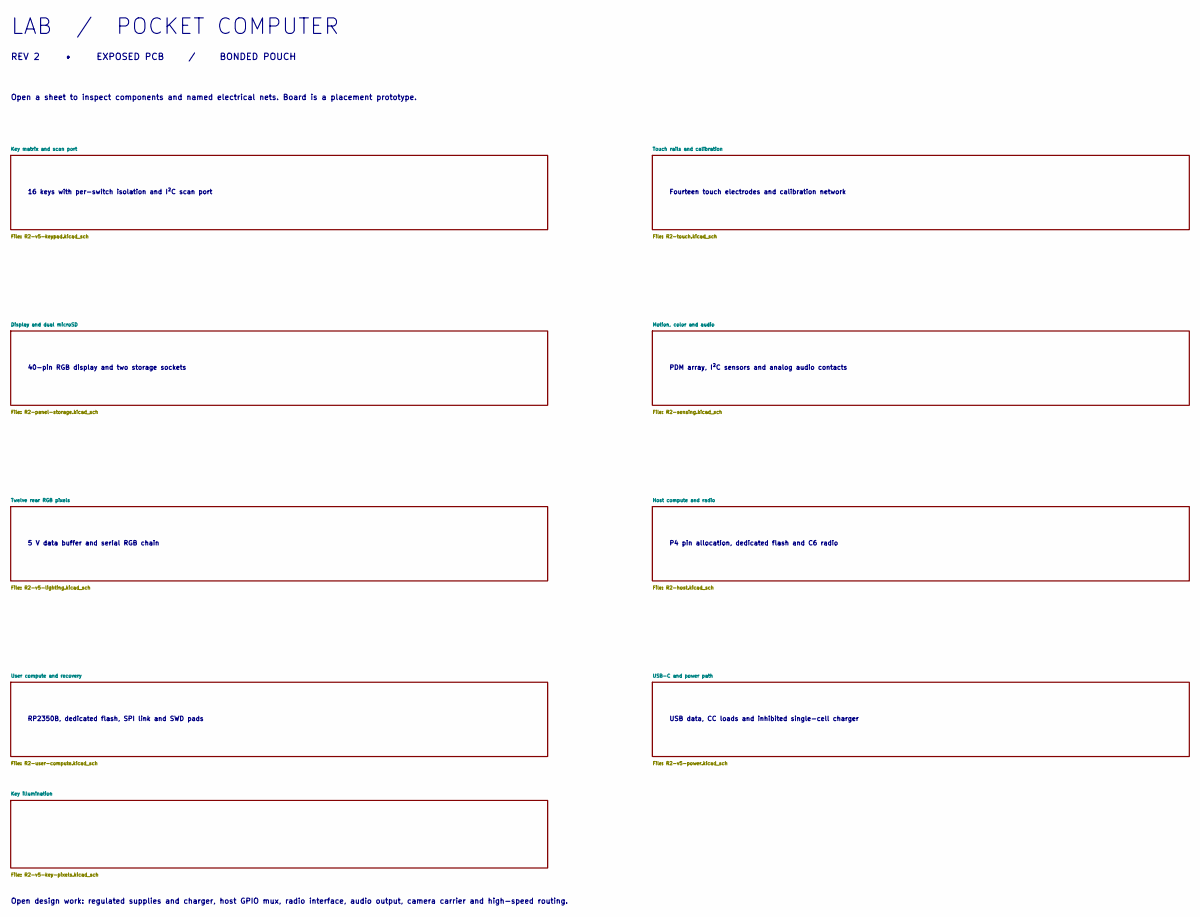
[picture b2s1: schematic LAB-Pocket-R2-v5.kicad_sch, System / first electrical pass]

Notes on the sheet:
LAB / POCKET COMPUTER
REV 2 • EXPOSED PCB / BONDED POUCH
Open a sheet to inspect components and named electrical nets. Board is a placement prototype.
16 keys with per-switch isolation and I²C scan port
Fourteen touch electrodes and calibration network
40-pin RGB display and two storage sockets
PDM array, I²C sensors and analog audio contacts
5 V data buffer and serial RGB chain
P4 pin allocation, dedicated flash and C6 radio
RP2350B, dedicated flash, SPI link and SWD pads
USB data, CC loads and inhibited single-cell charger
Open design work: regulated supplies and charger, host GPIO mux, radio interface, audio output, camera carrier and high-speed routing.

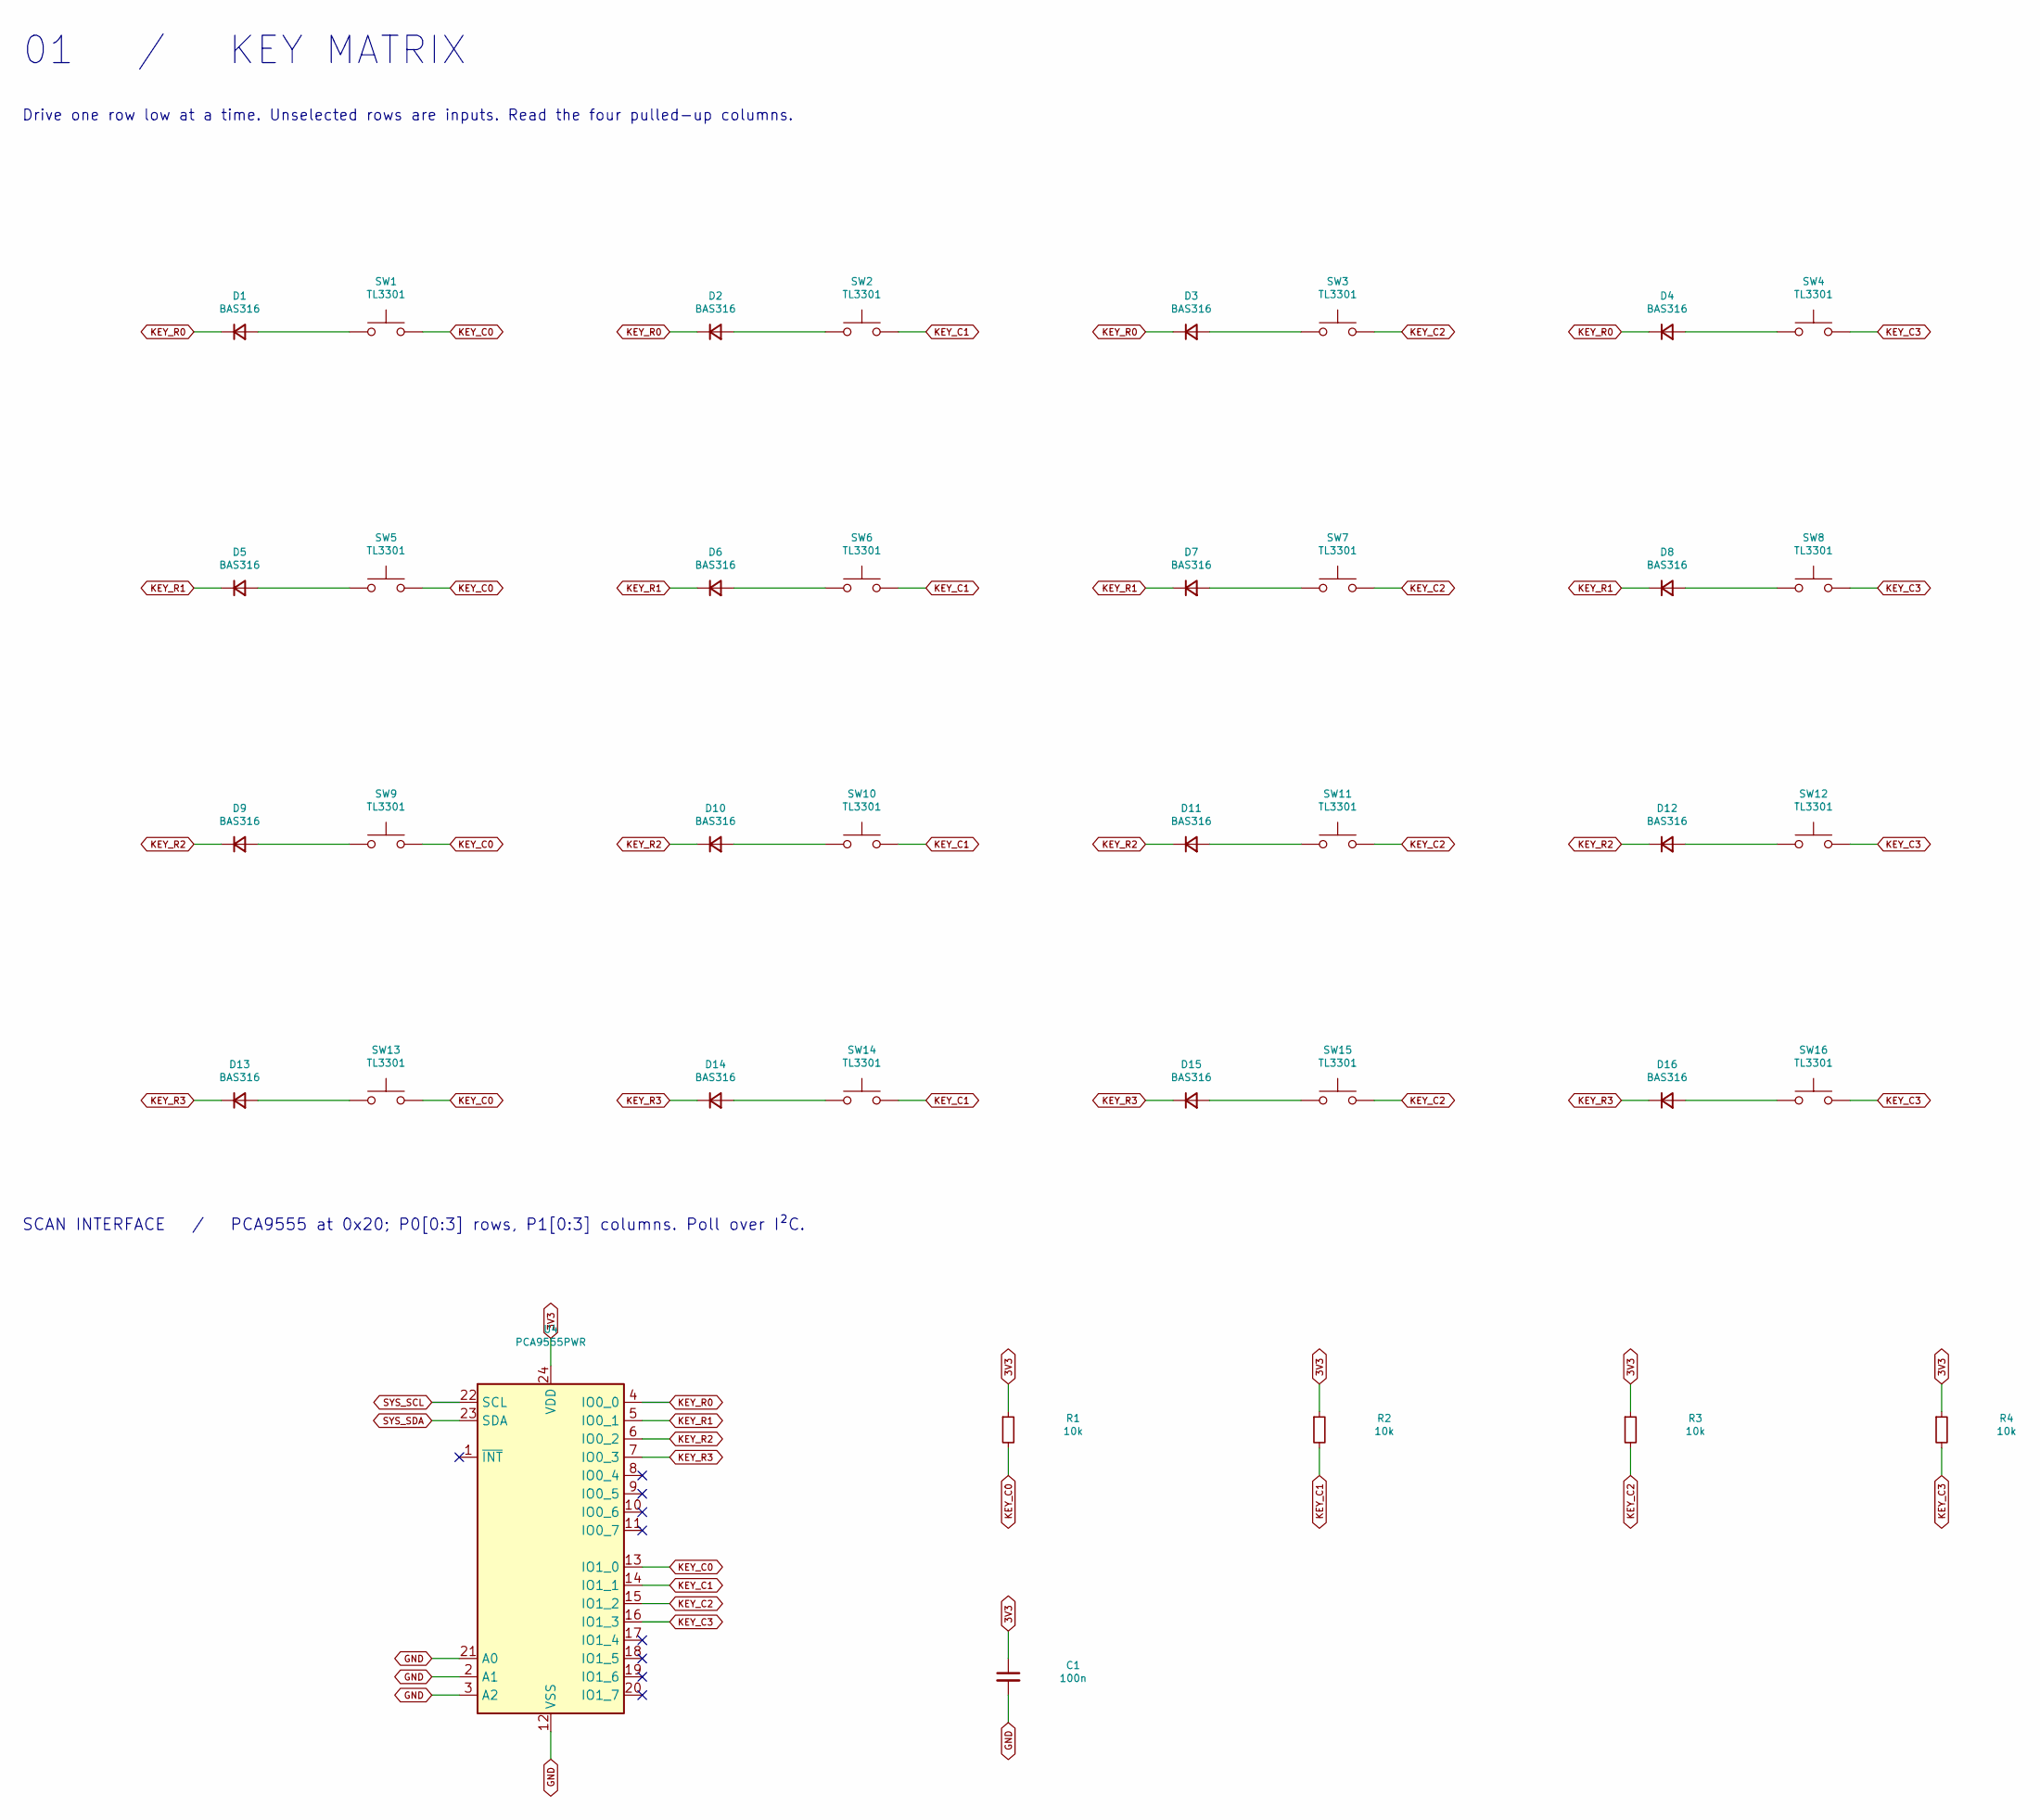
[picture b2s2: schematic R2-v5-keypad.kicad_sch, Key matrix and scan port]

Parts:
C1: 100n; C_0603_1608Metric; MPN C0603C104K5RACTU
D1, D2, D3, D4, D5, D6, D7, D8, D9, D10, D11, D12, D13, D14, D15, D16: BAS316; D_SOD-323; MPN BAS316,115
R1, R2, R3, R4: 10k; R_0603_1608Metric; MPN CRCW060310K0FKEA
SW1, SW2, SW3, SW4, SW5, SW6, SW7, SW8, SW9, SW10, SW11, SW12, SW13, SW14, SW15, SW16: TL3301; TL3301-key-v5; MPN TL3301NF160QG
U4: PCA9555PWR; TSSOP-24_4.4x7.8mm_P0.65mm; MPN PCA9555PWR

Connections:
3V3: C1.1, R1.1, R2.1, R3.1, R4.1, U4.24 (VDD); also elsewhere on the board
GND: C1.2, U4.2 (A1), U4.3 (A2), U4.12 (VSS), U4.21 (A0); also elsewhere on the board
KEY_C0: R1.2, SW1.2, SW5.2, SW9.2, SW13.2, U4.13 (IO1_0)
KEY_C1: R2.2, SW2.2, SW6.2, SW10.2, SW14.2, U4.14 (IO1_1)
KEY_C2: R3.2, SW3.2, SW7.2, SW11.2, SW15.2, U4.15 (IO1_2)
KEY_C3: R4.2, SW4.2, SW8.2, SW12.2, SW16.2, U4.16 (IO1_3)
KEY_R0: D1.1 (K), D2.1 (K), D3.1 (K), D4.1 (K), U4.4 (IO0_0)
KEY_R1: D5.1 (K), D6.1 (K), D7.1 (K), D8.1 (K), U4.5 (IO0_1)
KEY_R2: D9.1 (K), D10.1 (K), D11.1 (K), D12.1 (K), U4.6 (IO0_2)
KEY_R3: D13.1 (K), D14.1 (K), D15.1 (K), D16.1 (K), U4.7 (IO0_3)
unnamed: D1.2 (A), SW1.1
unnamed: D2.2 (A), SW2.1
unnamed: D3.2 (A), SW3.1
unnamed: D4.2 (A), SW4.1
unnamed: D5.2 (A), SW5.1
unnamed: D6.2 (A), SW6.1
unnamed: D7.2 (A), SW7.1
unnamed: D8.2 (A), SW8.1
unnamed: D9.2 (A), SW9.1
unnamed: D10.2 (A), SW10.1
unnamed: D11.2 (A), SW11.1
unnamed: D12.2 (A), SW12.1
unnamed: D13.2 (A), SW13.1
unnamed: D14.2 (A), SW14.1
unnamed: D15.2 (A), SW15.1
unnamed: D16.2 (A), SW16.1
SYS_SCL: U4.22 (SCL); also elsewhere on the board
SYS_SDA: U4.23 (SDA); also elsewhere on the board

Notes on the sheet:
01 / KEY MATRIX
Drive one row low at a time. Unselected rows are inputs. Read the four pulled-up columns.
SCAN INTERFACE / PCA9555 at 0x20; P0[0:3] rows, P1[0:3] columns. Poll over I²C.
